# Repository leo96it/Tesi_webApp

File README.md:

# Tesi_webApp

This project was made for the degree in computer engineering at Uninettuno.
It consist of a web server with a backend server, a mysql database and frontend web site. The server receive data from several hardware clients, based on ESP8266 or ESP32 microcontroller.

## Hardware - build with Arduino IDE v1.8.5 and KiCad v5

To run the hardware part, first you need to insert your wifi `SSID` and `password`, then you need to change the `serverURL` variable to match your local IP address.
Finally you can boot the firmware onto the ESP8266 devboard.
ATTENTION: the Arduino IDE require the download of card manager for ESP32 and ESP8266.

## Database - build with MySQL v8.0.28

Download MySQL with the MySQL installer (Windows) from:  https://dev.mysql.com/downloads/installer/.
Create the database called `ESP32_plant1` to match the variable `dbname` in config.json (backend).

## Server - build with NodeJS v14.17.5

Download all the module with `npm i` and start the MYSQL80 system variable. Then run `npm start`.

## Frontend - build with Angular CLI v13.0.3, NPM 6.14.14 and Grafana

First you need to set the Grafana dashboard, follow the PDF file `Elaborato finale - Barea Leonardo` in Extras folder, for the procedure and `query-Grafana` in Database folder for the query from Grafana to MySQL.
Run `ng serve` for a dev server. Navigate to `http://localhost:4200/`. The app will automatically reload if you change any of the source files.

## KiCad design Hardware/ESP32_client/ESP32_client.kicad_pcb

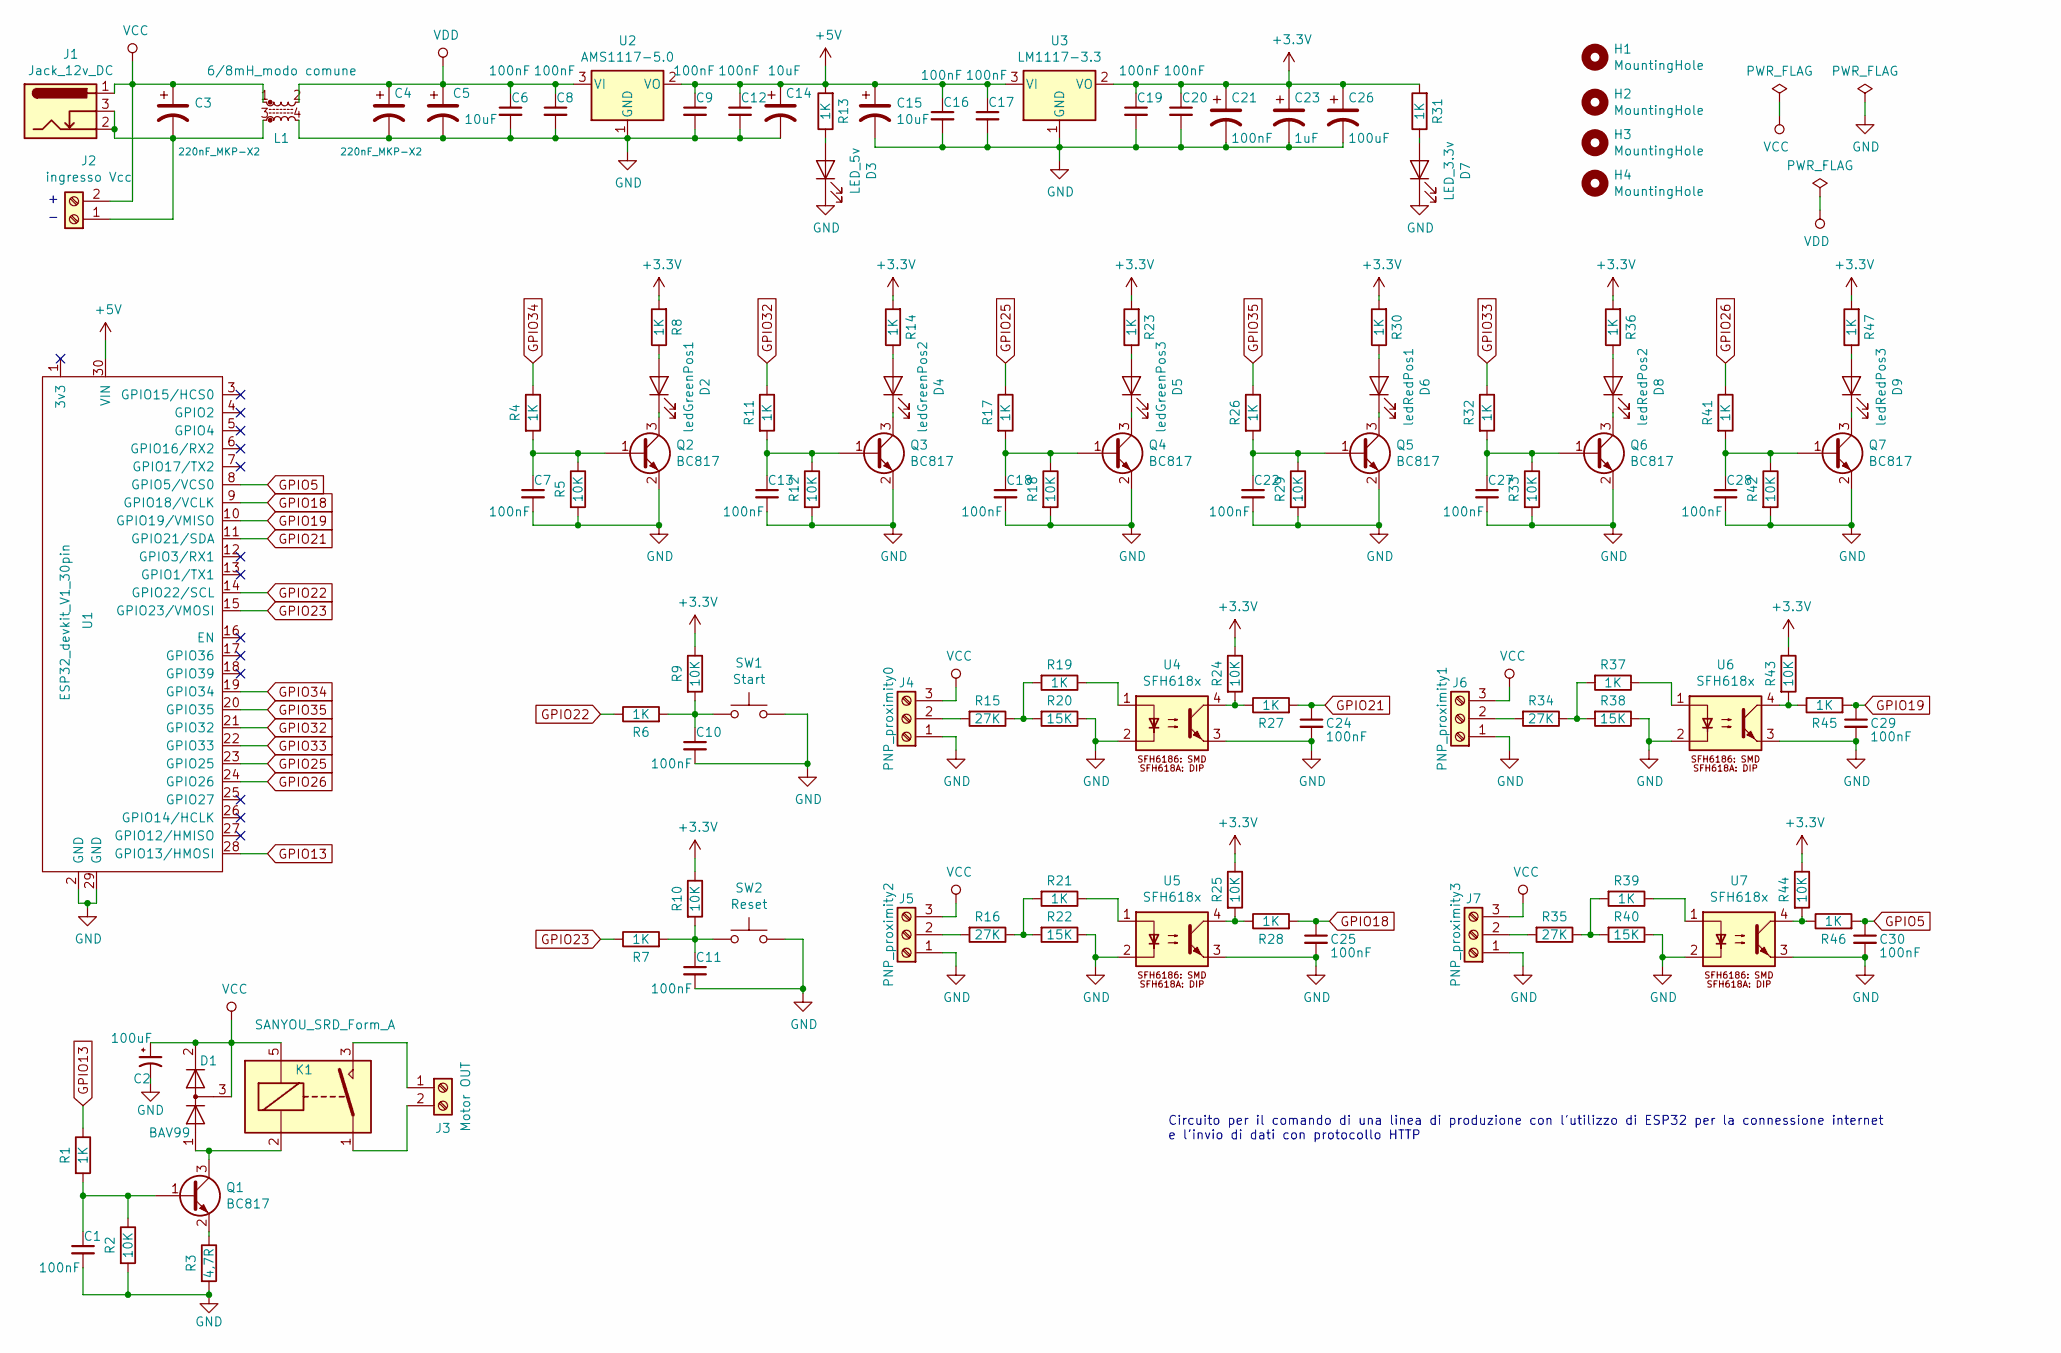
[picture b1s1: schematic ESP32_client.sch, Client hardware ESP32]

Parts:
C1, C6, C7, C8, C9, C10, C11, C12, C13, C16, C17, C18, C19, C20, C22, C24, C25, C27, C28, C29, C30: 100nF; C_0603_1608Metric
C2: 100uF; CP_Radial_D5.0mm_P2.50mm
C3, C4: 220nF_MKP-X2; C_Rect_L18.0mm_W7.0mm_P15.00mm_FKS3_FKP3
C5, C14, C15: 10uF; CP_Radial_D4.0mm_P2.00mm
C21: 100nF; CP_Radial_D4.0mm_P2.00mm
C23: 1uF; CP_Radial_D4.0mm_P2.00mm
C26: 100uF; CP_Radial_D4.0mm_P2.00mm
D1: BAV99; SOT-23
D2: ledGreenPos1; LED_0805_2012Metric
D3: LED_5v; LED_0805_2012Metric
D4: ledGreenPos2; LED_0805_2012Metric
D5: ledGreenPos3; LED_0805_2012Metric
D6: ledRedPos1; LED_0805_2012Metric
D7: LED_3.3v; LED_0805_2012Metric
D8: ledRedPos2; LED_0805_2012Metric
D9: ledRedPos3; LED_0805_2012Metric
H1, H2, H3, H4: MountingHole; MountingHole_3.2mm_M3
J1: Jack_12v_DC; jack_alimentazione_switchcraft
J2: ingresso Vcc; morsetto_2vie_P10.0mm
J3: Motor OUT; morsetto_2vie_P10.0mm
J4: PNP_proximity0; TerminalBlock_bornier-3_P5.08mm
J5: PNP_proximity2; TerminalBlock_bornier-3_P5.08mm
J6: PNP_proximity1; TerminalBlock_bornier-3_P5.08mm
J7: PNP_proximity3; TerminalBlock_bornier-3_P5.08mm
K1: SANYOU_SRD_Form_A; Relay_SPST_SANYOU_SRD_Series_Form_A
L1: 6/8mH_modo comune; Choke_Schaffner_RN204-04-9.0x14.0mm
Q1, Q2, Q3, Q4, Q5, Q6, Q7: BC817; SOT-23
R1, R4, R6, R7, R8, R11, R13, R14, R17, R19, R21, R23, R26, R27, R28, R30, R31, R32, R36, R37, R39, R41, R45, R46, R47: 1K; R_0603_1608Metric
R2, R5, R9, R10, R12, R18, R24, R25, R29, R33, R42, R43, R44: 10K; R_0603_1608Metric
R3: 4,7R; R_0603_1608Metric
R15, R16, R34, R35: 27K; R_0603_1608Metric
R20, R22, R38, R40: 15K; R_0603_1608Metric
SW1: Start; SW_PUSH_6mm
SW2: Reset; SW_PUSH_6mm
U1: ESP32_devkit_V1_30pin; esp32_devkit_v1_doit
U2: AMS1117-5.0; SOT-223-3_TabPin2
U3: LM1117-3.3; SOT-223-3_TabPin2
U4, U5, U6, U7: SFH618x; DIP-4_W7.62mm

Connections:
+3V3: C19.1, C20.1, C21.1, C23.1, C26.1, R8.2, R9.1, R10.1, R14.2, R23.2, R24.1, R25.1, R30.2, R31.2, R36.2, R43.1, R44.1, R47.2, U3.2 (VO)
+5V: C9.1, C12.1, C14.1, C15.1, C16.1, C17.1, R13.2, U1.30 (VIN), U2.2 (VO), U3.3 (VI)
GND: C1.2, C2.2, C4.2, C5.2, C6.2, C7.2, C8.2, C9.2, C10.2, C11.2, C12.2, C13.2, C14.2, C15.2, C16.2, C17.2, C18.2, C19.2, C20.2, C21.2, C22.2, C23.2, C24.2, C25.2, C26.2, C27.2, C28.2, C29.2, C30.2, D3.1 (K), D7.1 (K), J4.1, J5.1, J6.1, J7.1, L1.4, Q2.2 (E), Q3.2 (E), Q4.2 (E), Q5.2 (E), Q6.2 (E), Q7.2 (E), R2.2, R3.2, R5.2, R12.2, R18.2, R20.1, R22.1, R29.2, R33.2, R38.1, R40.1, R42.2, SW1.2, SW2.2, U1.2 (GND), U1.29 (GND), U2.1 (GND), U3.1 (GND), U4.2, U4.3, U5.2, U5.3, U6.2, U6.3, U7.2, U7.3
GPIO5: C30.1, R46.2, U1.8 (GPIO5/VCS0)
GPIO13: R1.1, U1.28 (GPIO13/HMOSI)
GPIO18: C25.1, R28.2, U1.9 (GPIO18/VCLK)
GPIO19: C29.1, R45.2, U1.10 (GPIO19/VMISO)
GPIO21: C24.1, R27.2, U1.11 (GPIO21/SDA)
GPIO22: R6.1, U1.14 (GPIO22/SCL)
GPIO23: R7.1, U1.15 (GPIO23/VMOSI)
GPIO25: R17.1, U1.23 (GPIO25)
GPIO26: R41.1, U1.24 (GPIO26)
GPIO32: R11.1, U1.21 (GPIO32)
GPIO33: R32.1, U1.22 (GPIO33)
GPIO34: R4.1, U1.19 (GPIO34)
GPIO35: R26.1, U1.20 (GPIO35)
unnamed: C1.1, Q1.1 (B), R1.2, R2.1
unnamed: C3.2, J1.2, J1.3, J2.1, L1.3
unnamed: C7.1, Q2.1 (B), R4.2, R5.1
unnamed: C10.1, R6.2, R9.2, SW1.1
unnamed: C11.1, R7.2, R10.2, SW2.1
unnamed: C13.1, Q3.1 (B), R11.2, R12.1
unnamed: C18.1, Q4.1 (B), R17.2, R18.1
unnamed: C22.1, Q5.1 (B), R26.2, R29.1
unnamed: C27.1, Q6.1 (B), R32.2, R33.1
unnamed: C28.1, Q7.1 (B), R41.2, R42.1
unnamed: D1.1 (K), K1.2, Q1.3 (C)
unnamed: D2.1 (K), Q2.3 (C)
unnamed: D2.2 (A), R8.1
unnamed: D3.2 (A), R13.1
unnamed: D4.1 (K), Q3.3 (C)
unnamed: D4.2 (A), R14.1
unnamed: D5.1 (K), Q4.3 (C)
unnamed: D5.2 (A), R23.1
unnamed: D6.1 (K), Q5.3 (C)
unnamed: D6.2 (A), R30.1
unnamed: D7.2 (A), R31.1
unnamed: D8.1 (K), Q6.3 (C)
unnamed: D8.2 (A), R36.1
unnamed: D9.1 (K), Q7.3 (C)
unnamed: D9.2 (A), R47.1
unnamed: J3.1, K1.3
unnamed: J3.2, K1.1
unnamed: J4.2, R15.2
unnamed: J5.2, R16.2
unnamed: J6.2, R34.2
unnamed: J7.2, R35.2
unnamed: Q1.2 (E), R3.1
unnamed: R15.1, R19.2, R20.2
unnamed: R16.1, R21.2, R22.2
unnamed: R19.1, U4.1
unnamed: R21.1, U5.1
unnamed: R24.2, R27.1, U4.4
unnamed: R25.2, R28.1, U5.4
unnamed: R34.1, R37.2, R38.2
unnamed: R35.1, R39.2, R40.2
unnamed: R37.1, U6.1
unnamed: R39.1, U7.1
unnamed: R43.2, R45.1, U6.4
unnamed: R44.2, R46.1, U7.4
VCC: C2.1, C3.1, D1.2 (A), D1.3 (K), J1.1, J2.2, J4.3, J5.3, J6.3, J7.3, K1.5, L1.1
VDD: C4.1, C5.1, C6.1, C8.1, L1.2, U2.3 (VI)

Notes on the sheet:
Circuito per il comando di una linea di produzione con l'utilizzo di ESP32 per la connessione internet e l'invio di dati con protocollo HTTP

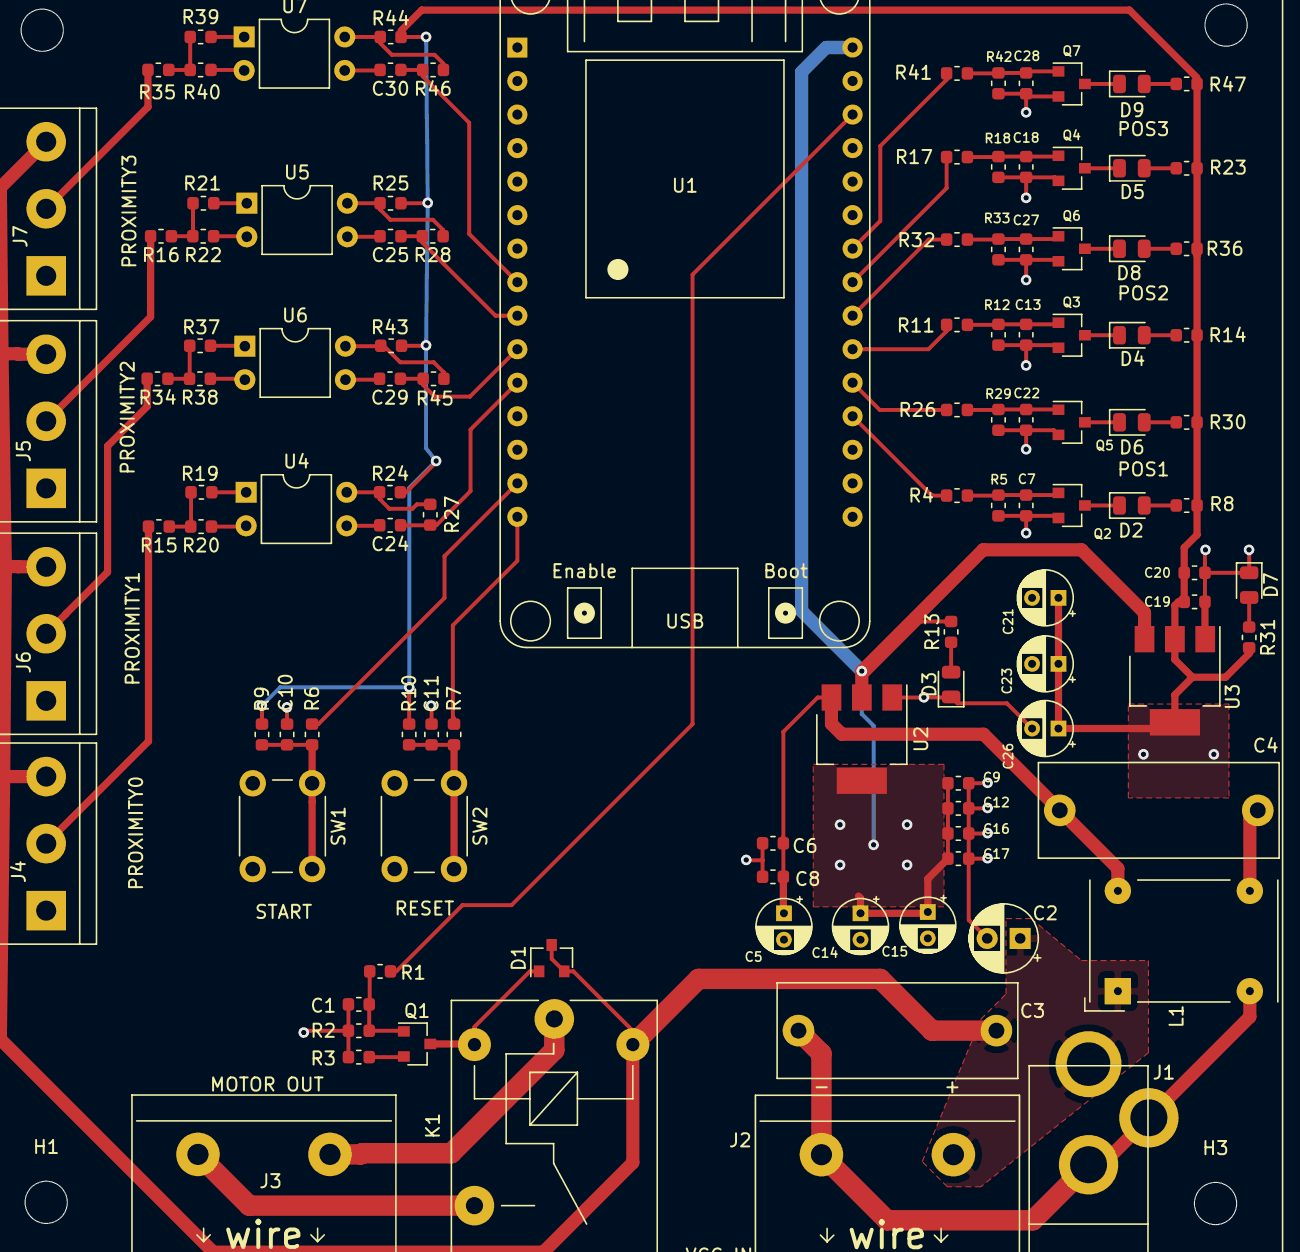
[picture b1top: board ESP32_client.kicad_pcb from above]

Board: 2 copper layers, 115 parts (0 on the bottom side), 62 nets.

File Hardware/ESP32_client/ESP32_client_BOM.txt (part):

Date:	21/02/2022 11:24					
Tool:	Eeschema (5.1.5)-3					
Component Count:	115					
						
Individual Components:						
						
Item	Qty	Reference(s)	Value	LibPart	Footprint	Datasheet
		C1	100nF	Device:C_Small	Capacitor_SMD:C_0603_1608Metric	~
		C2	100uF	Device:CP1_Small		~
		C3	220nF_MKP-X2	Device:CP1	Capacitor_THT:CP_Radial_D4.0mm_P2.00mm	~
		C4	220nF_MKP-X2	Device:CP1	Capacitor_THT:CP_Radial_D4.0mm_P2.00mm	~
		C5	10uF	Device:CP1	Capacitor_THT:CP_Radial_D4.0mm_P2.00mm	~
		C6	100nF	Device:C_Small	Capacitor_SMD:C_0603_1608Metric	~
		C7	100nF	Device:C_Small	Capacitor_SMD:C_0603_1608Metric	~
		C8	100nF	Device:C_Small	Capacitor_SMD:C_0603_1608Metric	~
		C9	100nF	Device:C_Small	Capacitor_SMD:C_0603_1608Metric	~
		C10	100nF	Device:C_Small	Capacitor_SMD:C_0603_1608Metric	~
		C11	100nF	Device:C_Small	Capacitor_SMD:C_0603_1608Metric	~
		C12	100nF	Device:C_Small	Capacitor_SMD:C_0603_1608Metric	~
		C13	100nF	Device:C_Small	Capacitor_SMD:C_0603_1608Metric	~
		C14	10uF	Device:CP1	Capacitor_THT:CP_Radial_D4.0mm_P2.00mm	~
		C15	10uF	Device:CP1	Capacitor_THT:CP_Radial_D4.0mm_P2.00mm	~
		C16	100nF	Device:C_Small	Capacitor_SMD:C_0603_1608Metric	~
		C17	100nF	Device:C_Small	Capacitor_SMD:C_0603_1608Metric	~
		C18	100nF	Device:C_Small	Capacitor_SMD:C_0603_1608Metric	~
		C19	100nF	Device:C_Small	Capacitor_SMD:C_0603_1608Metric	~
		C20	100nF	Device:C_Small	Capacitor_SMD:C_0603_1608Metric	~
		C21	100nF	Device:CP1	Capacitor_THT:CP_Radial_D4.0mm_P2.00mm	~
		C22	100nF	Device:C_Small	Capacitor_SMD:C_0603_1608Metric	~
		C23	1uF	Device:CP1	Capacitor_THT:CP_Radial_D4.0mm_P2.00mm	~
		C24	100nF	Device:C_Small	Capacitor_SMD:C_0603_1608Metric	~
		C25	100nF	Device:C_Small	Capacitor_SMD:C_0603_1608Metric	~
		C26	100uF	Device:CP1	Capacitor_THT:CP_Radial_D4.0mm_P2.00mm	~
		C27	100nF	Device:C_Small	Capacitor_SMD:C_0603_1608Metric	~
		C28	100nF	Device:C_Small	Capacitor_SMD:C_0603_1608Metric	~
		C29	100nF	Device:C_Small	Capacitor_SMD:C_0603_1608Metric	~
		C30	100nF	Device:C_Small	Capacitor_SMD:C_0603_1608Metric	~
		D1	BAV99	Diode:BAV99	Package_TO_SOT_SMD:SOT-23	https://assets.nexperia.com/documents/data-sheet/BAV99_SER.pdf
		D2	ledGreenPos1	Device:LED	LED_SMD:LED_0805_2012Metric	~
		D3	LED_5v	Device:LED	LED_SMD:LED_0805_2012Metric	~
		D4	ledGreenPos2	Device:LED	LED_SMD:LED_0805_2012Metric	~
		D5	ledGreenPos3	Device:LED	LED_SMD:LED_0805_2012Metric	~
		D6	ledRedPos1	Device:LED	LED_SMD:LED_0805_2012Metric	~
		D7	LED_3.3v	Device:LED	LED_SMD:LED_0805_2012Metric	~
		D8	ledRedPos2	Device:LED	LED_SMD:LED_0805_2012Metric	~
		D9	ledRedPos3	Device:LED	LED_SMD:LED_0805_2012Metric	~
		H1	MountingHole	Mechanical:MountingHole	MountingHole:MountingHole_3.2mm_M3	~
		H2	MountingHole	Mechanical:MountingHole	MountingHole:MountingHole_3.2mm_M3	~
		H3	MountingHole	Mechanical:MountingHole	MountingHole:MountingHole_3.2mm_M3	~
		H4	MountingHole	Mechanical:MountingHole	MountingHole:MountingHole_3.2mm_M3	~
		J1	Jack_12v_DC	Connector:Barrel_Jack_Switch	Librerie_LEO:jack_alimentazione_switchcraft	~
		J2	ingresso Vcc	Connector:Screw_Terminal_01x02	Librerie_LEO:morsetto_2vie_grande	~
		J3	Motor OUT	Connector:Screw_Terminal_01x02		~
		J4	PNP_proximity0	Connector:Screw_Terminal_01x03		~
		J5	PNP_proximity2	Connector:Screw_Terminal_01x03		~
		J6	PNP_proximity1	Connector:Screw_Terminal_01x03		~
		J7	PNP_proximity3	Connector:Screw_Terminal_01x03		~
		K1	SANYOU_SRD_Form_A	Relay:SANYOU_SRD_Form_A	Relay_THT:Relay_SPST_SANYOU_SRD_Series_Form_A	http://www.sanyourelay.ca/public/products/pdf/SRD.pdf
		L1	6/8mH_modo comune	Device:L_Core_Ferrite_Coupled_Small		~
		Q1	BC817	Transistor_BJT:BC817	Package_TO_SOT_SMD:SOT-23	http://www.fairchildsemi.com/ds/BC/BC817.pdf
		Q2	BC817	Transistor_BJT:BC817	Package_TO_SOT_SMD:SOT-23	http://www.fairchildsemi.com/ds/BC/BC817.pdf
		Q3	BC817	Transistor_BJT:BC817	Package_TO_SOT_SMD:SOT-23	http://www.fairchildsemi.com/ds/BC/BC817.pdf
		Q4	BC817	Transistor_BJT:BC817	Package_TO_SOT_SMD:SOT-23	http://www.fairchildsemi.com/ds/BC/BC817.pdf
		Q5	BC817	Transistor_BJT:BC817	Package_TO_SOT_SMD:SOT-23	http://www.fairchildsemi.com/ds/BC/BC817.pdf
		Q6	BC817	Transistor_BJT:BC817	Package_TO_SOT_SMD:SOT-23	http://www.fairchildsemi.com/ds/BC/BC817.pdf
		Q7	BC817	Transistor_BJT:BC817	Package_TO_SOT_SMD:SOT-23	http://www.fairchildsemi.com/ds/BC/BC817.pdf
		R1	1K	Device:R	Resistor_SMD:R_0603_1608Metric	~
		R2	10K	Device:R	Resistor_SMD:R_0603_1608Metric	~
		R3	4,7R	Device:R	Resistor_SMD:R_0603_1608Metric	~
		R4	1K	Device:R	Resistor_SMD:R_0603_1608Metric	~
		R5	10K	Device:R	Resistor_SMD:R_0603_1608Metric	~
		R6	1K	Device:R	Resistor_SMD:R_0603_1608Metric	~
		R7	1K	Device:R	Resistor_SMD:R_0603_1608Metric	~
		R8	1K	Device:R	Resistor_SMD:R_0603_1608Metric	~
		R9	10K	Device:R	Resistor_SMD:R_0603_1608Metric	~
		R10	10K	Device:R	Resistor_SMD:R_0603_1608Metric	~
		R11	1K	Device:R	Resistor_SMD:R_0603_1608Metric	~
		R12	10K	Device:R	Resistor_SMD:R_0603_1608Metric	~
		R13	1K	Device:R	Resistor_SMD:R_0603_1608Metric	~
		R14	1K	Device:R	Resistor_SMD:R_0603_1608Metric	~
		R15	27K	Device:R	Resistor_SMD:R_0603_1608Metric	~
		R16	27K	Device:R	Resistor_SMD:R_0603_1608Metric	~
		R17	1K	Device:R	Resistor_SMD:R_0603_1608Metric	~
		R18	10K	Device:R	Resistor_SMD:R_0603_1608Metric	~
		R19	1K	Device:R	Resistor_SMD:R_0603_1608Metric	~
		R20	15K	Device:R	Resistor_SMD:R_0603_1608Metric	~
		R21	1K	Device:R	Resistor_SMD:R_0603_1608Metric	~
		R22	15K	Device:R	Resistor_SMD:R_0603_1608Metric	~
		R23	1K	Device:R	Resistor_SMD:R_0603_1608Metric	~
		R24	10K	Device:R	Resistor_SMD:R_0603_1608Metric	~
		R25	10K	Device:R	Resistor_SMD:R_0603_1608Metric	~
		R26	1K	Device:R	Resistor_SMD:R_0603_1608Metric	~
		R27	1K	Device:R	Resistor_SMD:R_0603_1608Metric	~
		R28	1K	Device:R	Resistor_SMD:R_0603_1608Metric	~
		R29	10K	Device:R	Resistor_SMD:R_0603_1608Metric	~
		R30	1K	Device:R	Resistor_SMD:R_0603_1608Metric	~
		R31	1K	Device:R	Resistor_SMD:R_0603_1608Metric	~
		R32	1K	Device:R	Resistor_SMD:R_0603_1608Metric	~
		R33	10K	Device:R	Resistor_SMD:R_0603_1608Metric	~
		R34	27K	Device:R	Resistor_SMD:R_0603_1608Metric	~
		R35	27K	Device:R	Resistor_SMD:R_0603_1608Metric	~
		R36	1K	Device:R	Resistor_SMD:R_0603_1608Metric	~
		R37	1K	Device:R	Resistor_SMD:R_0603_1608Metric	~
		R38	15K	Device:R	Resistor_SMD:R_0603_1608Metric	~
		R39	1K	Device:R	Resistor_SMD:R_0603_1608Metric	~
		R40	15K	Device:R	Resistor_SMD:R_0603_1608Metric	~
		R41	1K	Device:R	Resistor_SMD:R_0603_1608Metric	~
		R42	10K	Device:R	Resistor_SMD:R_0603_1608Metric	~
		R43	10K	Device:R	Resistor_SMD:R_0603_1608Metric	~
		R44	10K	Device:R	Resistor_SMD:R_0603_1608Metric	~
		R45	1K	Device:R	Resistor_SMD:R_0603_1608Metric	~
		R46	1K	Device:R	Resistor_SMD:R_0603_1608Metric	~
		R47	1K	Device:R	Resistor_SMD:R_0603_1608Metric	~
		SW1	Start	Switch:SW_Push		~
		SW2	Start	Switch:SW_Push		~
		U1	ESP32_devkit_V1_30pin	Librerie_LEO:ESP32_devkit_V1_30pin		
		U2	AMS1117-5.0	Regulator_Linear:AMS1117-5.0	Package_TO_SOT_SMD:SOT-223-3_TabPin2	http://www.advanced-monolithic.com/pdf/ds1117.pdf
		U3	LM1117-3.3	Regulator_Linear:LM1117-3.3	Package_TO_SOT_SMD:SOT-223-3_TabPin2	http://www.ti.com/lit/ds/symlink/lm1117.pdf
		U4	SFH618x	Librerie_LEO:SFH618x		
		U5	SFH618x	Librerie_LEO:SFH618x		
		U6	SFH618x	Librerie_LEO:SFH618x		
		U7	SFH618x	Librerie_LEO:SFH618x		
						
						
						
Collated Components:						
						
Item	Qty	Reference(s)	Value	LibPart	Footprint	Datasheet
1	21	C1, C6, C7, C8, C9, C10, C11, C12, C13, C16, C17, C18, C19, C20, C22, C24, C25, C27, C28, C29, C30	100nF	Device:C_Small	Capacitor_SMD:C_0603_1608Metric	~
2	1	C2	100uF	Device:CP1_Small		~
3	2	C3, C4	220nF_MKP-X2	Device:CP1	Capacitor_THT:CP_Radial_D4.0mm_P2.00mm	~
4	3	C5, C14, C15	10uF	Device:CP1	Capacitor_THT:CP_Radial_D4.0mm_P2.00mm	~
5	1	C21	100nF	Device:CP1	Capacitor_THT:CP_Radial_D4.0mm_P2.00mm	~
6	1	C23	1uF	Device:CP1	Capacitor_THT:CP_Radial_D4.0mm_P2.00mm	~
7	1	C26	100uF	Device:CP1	Capacitor_THT:CP_Radial_D4.0mm_P2.00mm	~
8	1	D1	BAV99	Diode:BAV99	Package_TO_SOT_SMD:SOT-23	https://assets.nexperia.com/documents/data-sheet/BAV99_SER.pdf
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
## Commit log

2022-03-13 update server code
2022-03-13 added firmware test
2022-03-19 corrected error code
2022-03-19 Add extras folder
2022-03-20 Added Elaborato
2022-03-24 Time range adjusted
2022-03-24 fixed git bug
